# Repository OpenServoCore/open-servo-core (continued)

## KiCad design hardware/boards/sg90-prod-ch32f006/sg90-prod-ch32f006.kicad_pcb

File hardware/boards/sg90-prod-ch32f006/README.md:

# SG90 Servo Controller Board - CH32V006

A compact, high-precision servo controller designed to replace the control circuitry in SG90/MG90 servo clones. This single-sided board fits within a 10x12.5mm footprint while providing advanced features like back-EMF sensing, overcurrent protection, and 0.1-0.2° position precision.

## Features

- **MCU**: CH32V006F8U6 RISC-V microcontroller (48MHz, 32KB flash, 4KB RAM)
- **Motor Driver**: Integrated DRV8837C H-bridge (1.8A peak)
- **Position Sensing**: 12-bit ADC with RC filtering for 0.1-0.2° precision
- **Current Sensing**: 0.1Ω shunt with internal op-amp
- **Protection**: P-channel MOSFET reverse polarity protection (17mΩ RDS(on))
- **Communication**: 2Mbps half-duplex UART over single DATA line
- **Power**: 5V operation, no LDO required
- **Size**: 10x12.5mm, single-sided assembly
- **Debug**: 4-pin SWD interface for programming with WCH-LinkE

## Specifications

- Input Voltage: 4.5-5.5V
- Continuous Current: 200mA (typical servo operation)
- Peak Current: 1A (stall condition)
- Position Resolution: 0.044°/count (4096 counts over 180°)
- PWM Frequency: 10kHz center-aligned
- Communication: 2Mbps half-duplex UART
- Temperature Range: -40°C to +85°C

## Bill of Materials (BOM)

| Ref | Description | Package | LCSC # | Qty | Unit Price @5 | Unit Price @150 | Unit Price @500 |
|-----|-------------|---------|--------|-----|---------------|-----------------|-----------------|
| U1 | CH32V006F8U6 MCU | QFN-20 3x3mm | C42431288 | 1 | $0.2643 | $0.1838 | $0.1537 |
| U2 | DRV8837CDSGR Motor Driver | WSON-8 | C191000 | 1 | $0.098 | $0.0666 | $0.0587 |
| U3 | 74LVC1G07DSFR Buffer | TDFN-6 1x1mm | C42445855 | 1 | $0.0466 | $0.0317 | $0.0280 |
| Q1 | BRCS150P02ZJ P-MOSFET | DFN-6 2x2mm | C22448985 | 1 | $0.0747 | $0.0522 | $0.0466 |
| R1 | 10kΩ 1% | 0603 | Generic | 1 | $0.01 | $0.002 | $0.002 |
| R2 | 0.1Ω 1% 1/4W | 0603/0805 | Generic | 1 | $0.02 | $0.003 | $0.003 |
| R3 | 10kΩ 1% | 0603 | Generic | 1 | $0.01 | $0.002 | $0.002 |
| R4,R5 | 10kΩ 1% | 0603 | Generic | 2 | $0.01 | $0.002 | $0.002 |
| R6,R7 | 0Ω | 0603 | Generic | 2 | $0.01 | $0.001 | $0.001 |
| R8 | 0Ω | 0603 | Generic | 1 | $0.01 | $0.001 | $0.001 |
| R9 | 10kΩ 1% | 0603 | Generic | 1 | $0.01 | $0.002 | $0.002 |
| R10 | 1kΩ 1% | 0603 | Generic | 1 | $0.01 | $0.002 | $0.002 |
| C1,C2 | 100nF 16V X7R | 0603 | Generic | 2 | $0.01 | $0.002 | $0.002 |
| C3 | 1µF 16V X7R | 0603 | Generic | 1 | $0.01 | $0.003 | $0.003 |
| C4,C5 | 10µF 10V X5R | 0603/0805 | Generic | 2 | $0.02 | $0.005 | $0.004 |
| C6 | 100nF 16V X7R | 0603 | Generic | 1 | $0.01 | $0.002 | $0.002 |
| **Components Total** | | | | | **$0.664** | **~$0.35** | **$0.326** |
| **PCB** | 10x12.5mm 4-layer | - | - | 1 | **$1.40** | **$0.25** | **$0.11** |
| **TOTAL per board** | | | | | **$2.064** | **$0.60** | **$0.436** |
| **TOTAL** | | | | | **$10.32** | **$90.00** | **$218.00** |

### Cost Breakdown by Quantity

#### Prototype Run (5 boards)
- Components (5 sets): $0.664 × 5 = $3.32
- PCB (5 boards): $2.00 + $5.00 shipping = $7.00
- **Total for 5 boards: $10.32**
- **Cost per board: $2.06**
- **Selling at $3/board: $15 revenue - Profit: $4.68 (45% margin)**
- **Selling at $5/board: $25 revenue - Profit: $14.68 (142% margin)**

#### Small Production (150 boards)
- Components (150 sets): ~$0.35 × 150 = $52.50
- PCB (150 boards): $32.00 + $5.00 shipping = $37.00
- **Total for 150 boards: $89.50**
- **Cost per board: $0.60**
- **Selling at $2-3/board: $300-450 revenue**
- **Gross profit: $210.50-360.50**

#### Medium Production (500 boards)
- Components (500 sets): $0.326 × 500 = $163.00
- PCB (500 boards): $50.20 + $5.00 shipping = $55.20
- **Total for 500 boards: $218.20**
- **Cost per board: $0.44**
- **Selling at $2/board: $1,000 revenue**
- **Gross profit: $781.80 (358% markup!)**

*Prices shown are from LCSC in USD. Passive component prices are estimates for generic parts.*

## Pinout

### Power Connector (J1) - 3 pins
1. V_IN (5V)
2. DATA (Half-duplex UART, 2Mbps)
3. GND

### Motor Connector (J3) - 2 wire pads
1. MOT_A - Motor terminal A (7.4mm spacing)
2. MOT_B - Motor terminal B

### Potentiometer Connector (J2) - 3 pads
1. POT_VCC - Potentiometer power (5V)
2. POT_WIPER - Position feedback
3. POT_GND - Potentiometer ground

### Debug Interface (J4) - 4 pads, 1.27mm pitch
1. 5V - Power from debugger
2. GND - Ground
3. SWDIO - Single-wire debug
4. NC - Not connected

## Design Notes

### Power Architecture
- Single 5V rail operation eliminates need for LDO
- P-channel MOSFET provides reverse polarity protection with only 17mV drop at 1A
- Bulk capacitance (2x10µF) handles motor transients
- No ferrite bead needed due to synchronized ADC sampling

### ADC Precision
- 12-bit ADC provides 22.8 counts per degree (0.044°/count theoretical)
- RC filter (1kΩ + 100nF) on POT input reduces wiper noise
- 4-16x oversampling in firmware improves effective resolution
- Center-aligned PWM with mid-duty ADC sampling avoids switching noise

### Current Sensing
- 0.1Ω shunt resistor in series with motor ground
- Internal op-amp amplifies voltage drop
- ADC watchdog enables hardware overcurrent protection
- Kelvin connections (0Ω resistors R6,R7) for accurate sensing

### Communication
- Half-duplex UART at 2Mbps over single DATA line
- 74LVC1G07 open-drain buffer enables bidirectional communication
- 10kΩ pullup (R1) sized for 2Mbps operation
- Compatible with standard servo protocols

## Assembly

This board is designed for single-sided assembly, making it ideal for:
- Hot plate reflow
- Hot air station
- IR oven
- JLCPCB assembly service

All components are on the top side with no vias in pads.

## Programming

Program using WCH-LinkE debugger/programmer:
- Supports 5V target voltage
- Single-wire debug (SWD) interface
- Compatible with MounRiver Studio IDE
- printf debugging available over SWD

## Mechanical Integration

The board is designed to fit inside standard SG90 servo cases:
- Motor wires solder directly to MOT_A/MOT_B pads
- Potentiometer wires connect to J2
- Servo cable connects to J1
- Debug pads accessible through case opening

## Performance Targets

- Position accuracy: ±0.1-0.2°
- Position resolution: 0.044°
- Update rate: 10kHz
- Current limit: 1A (configurable via firmware)
- Continuous operation: 200mA
- Response time: <1ms
- Backdrive detection: Yes (via back-EMF)

## Manufacturing

Optimized for low-cost production:
- Total BOM cost: ~$0.43 at 500 qty
- Single-sided assembly reduces assembly cost
- Standard 0603 passives (except current shunt)
- All components available from LCSC
- 4-layer PCB for better thermal management

## TODO / Future Improvements

### Critical Values to Double-Check Before PCB Routing
- [ ] **Current shunt (R2):** Verify 0.1Ω gives good ADC range (0-330mV at 1A through 3.3x op-amp gain)
- [ ] **Voltage dividers (R4/R5):** Confirm 10kΩ divider properly scales 5V motor to ADC range
- [ ] **UART pullup (R1):** Verify 10kΩ optimal for 2Mbps half-duplex
- [ ] **RC filter (R10/C6):** Check 1kΩ + 100nF = 1.6kHz cutoff for POT noise
- [ ] **Bulk caps (C4/C5):** Confirm 2x10µF sufficient for motor transients
- [ ] **P-MOSFET RDS(on):** Verify 17mΩ = 17mV drop at 1A peak is acceptable
- [ ] **Motor pad spacing:** Confirm 7.4mm (3.7mm each side from center)
- [ ] **Debug pad pitch:** Verify 1.27mm for pogo pins
- [ ] **Package sizes:** Verify all footprints match actual parts (especially QFN-20)

### Rev B Changes
1. **Add test points on back side**
   - Add second 1x4 array at 1.27mm pitch (same as debug interface)
   - Uses same pogo pin clip for both programming and testing
   - **Debug array (1x4):** 5V, GND, SWDIO, NC (existing)
   - **Test array (1x4):** SEN_I, SEN_POT, PWM_A, V_MCU
   - Both arrays accessible from back when installed in servo
   - *Rationale: Single pogo clip tool works for both debug and test*

2. **Add ESD protection**
   - TVS diode on DATA line (SOD-523 or 0402 package)
   - Protects against ESD during cable plug/unplug
   - Suggested part: PESD5V0S1BL or similar 5.5V TVS (~$0.05)

3. **Consider fiducial marker**
   - Single 1mm fiducial for JLCPCB assembly alignment
   - Only if assembly house requires it

### Firmware Features (Planned)
- Backlash compensation
- Temperature compensation
- Position calibration LUT
- Multi-drop addressing
- Synchronized motion commands

## License

[Add your license here]

## Author

[Add author information here]

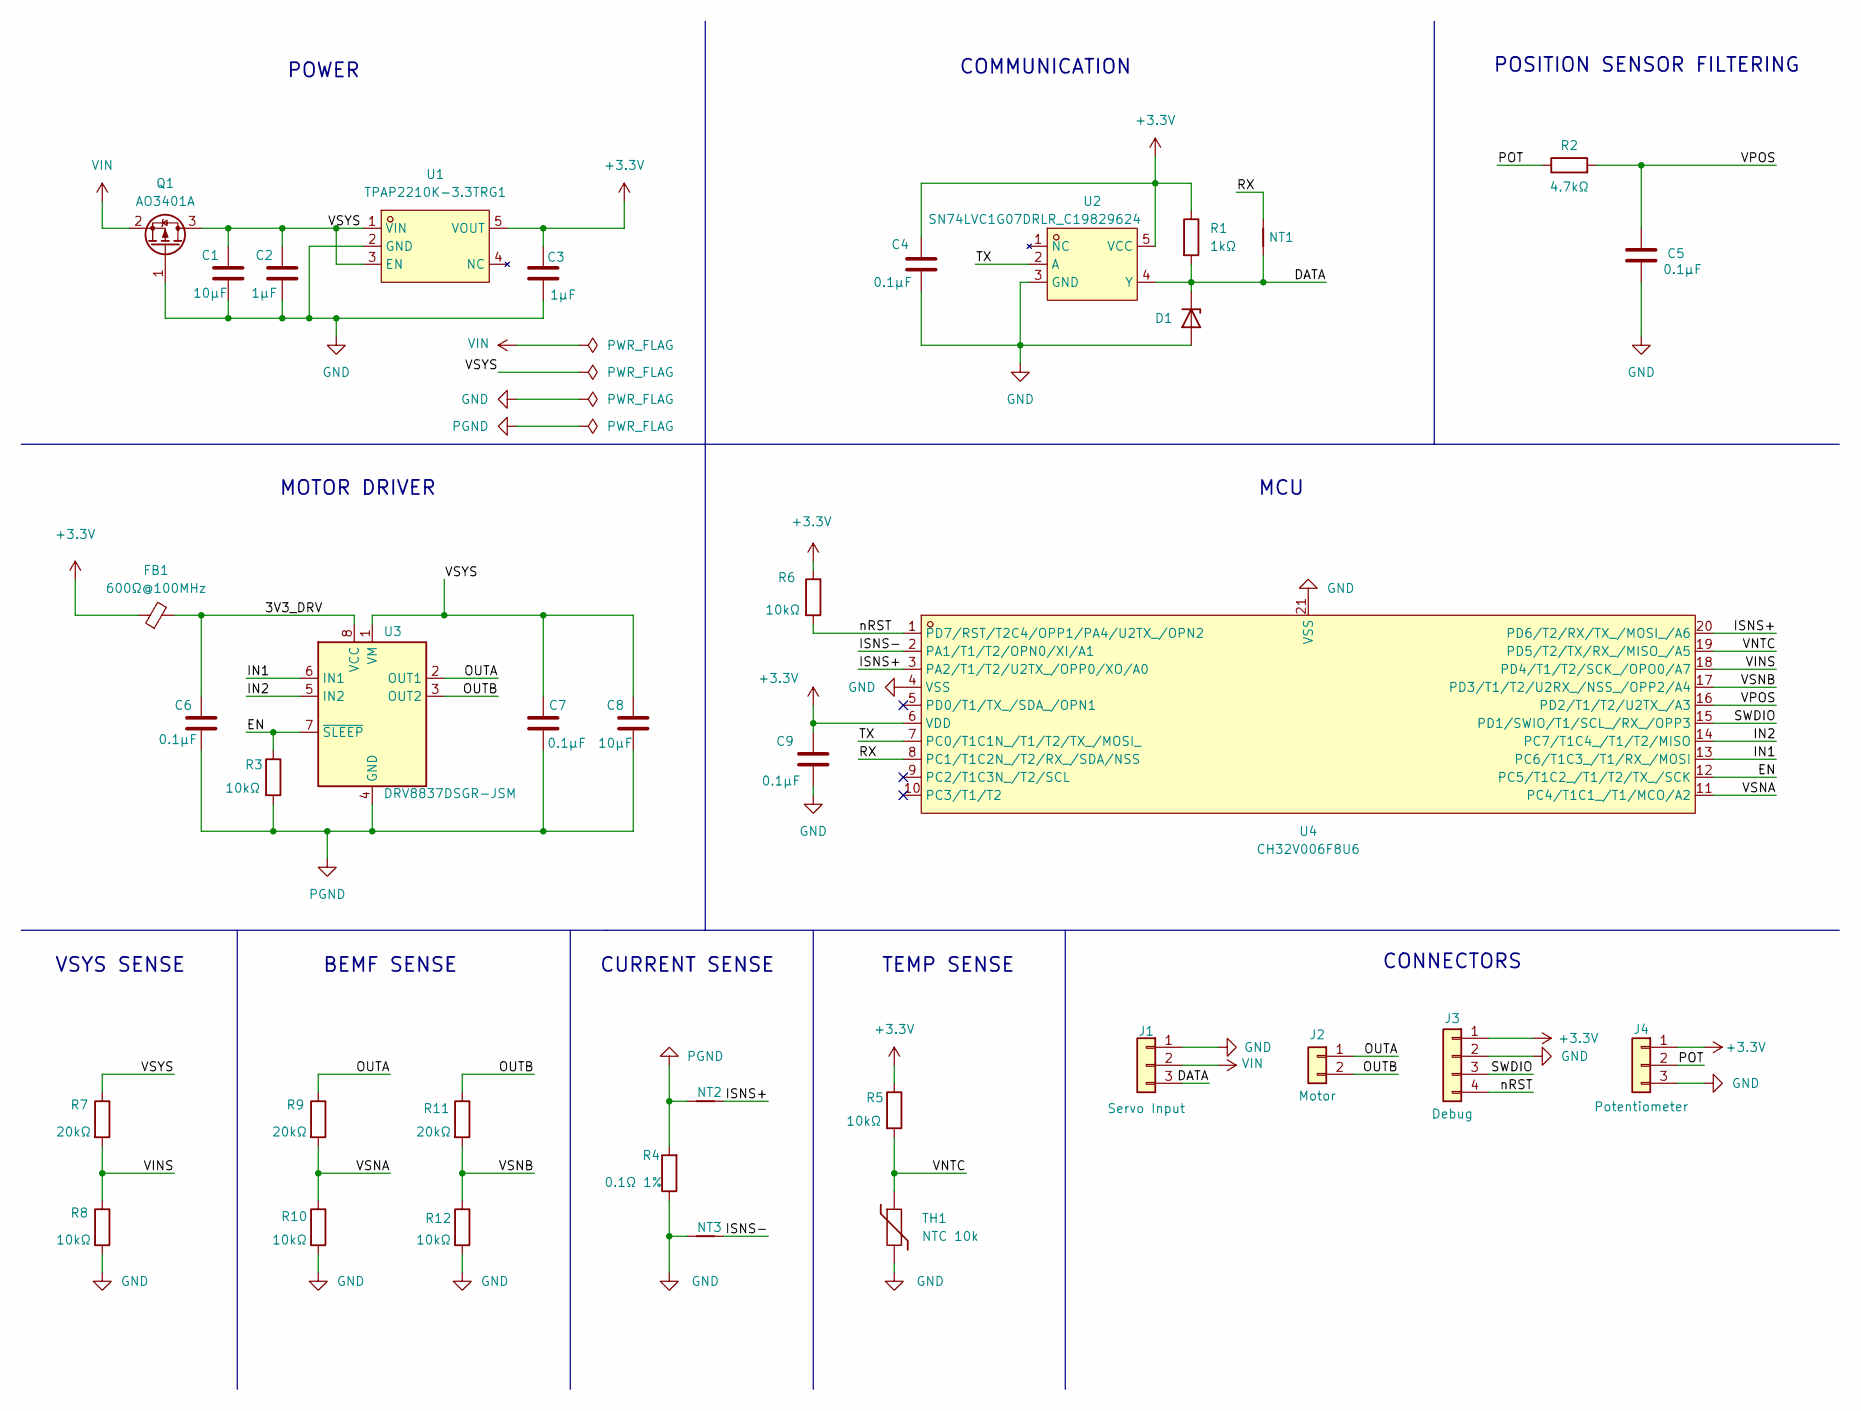
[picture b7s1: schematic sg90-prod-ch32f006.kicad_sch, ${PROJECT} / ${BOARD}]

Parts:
C1, C8: 10µF; C_0603_1608Metric
C2, C3: 1µF; C_0402_1005Metric
C4, C5, C6, C7, C9: 0.1µF; C_0402_1005Metric
D1: PESD5V0L1UL; D_SOD-882
FB1: 600Ω@100MHz; L_0603_1608Metric
J1: Servo Input; Servo_Output_Pads
J2: Motor; Motor_Wire_Pads
J3: Debug; Debug_Pads_1x4_P1.27mm
J4: Potentiometer; Pot_Wire_Pads
NT1, NT2, NT3: NetTie_2; NetTie-2_SMD_0.2mm
Q1: AO3401A; SOT-23
R1: 1kΩ; R_0402_1005Metric
R2: 4.7kΩ; R_0402_1005Metric
R3, R5, R6, R8, R10, R12: 10kΩ; R_0402_1005Metric
R4: 0.1Ω 1%; R_1206_3216Metric
R7, R9, R11: 20kΩ; R_0402_1005Metric
TH1: NTC 10k; R_0402_1005Metric
U1: TPAP2210K-3.3TRG1; SOT-23-5_L2.9-W1.6-P0.95-LS2.8-BR; LCSC Part C49190789
U2: SN74LVC1G07DRLR_C19829624; SOT-553-5_L1.6-W1.2-P0.50-LS1.6-BL; LCSC Part C19829624
U3: DRV8837DSGR-JSM; WSON-8-1EP_2x2mm_P0.5mm_EP0.9x1.6mm; LCSC C22447132
U4: CH32V006F8U6; UQFN-20_L3.0-W3.0-P0.40-BL-EP1.7; LCSC Part C42431288

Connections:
+3.3V: C3.1, C4.1, C9.1, FB1.1, J3.1, J4.1, R1.1, R5.1, R6.1, U1.5 (VOUT), U2.5 (VCC), U4.6 (VDD)
/3V3_DRV: C6.1, FB1.2, U3.8 (VCC)
/DATA: D1.1 (K), J1.3, NT1.2, R1.2, U2.4 (Y)
/EN: R3.1, U3.7 (~SLEEP), U4.12 (PC5/T1C2_/T1/T2/TX_/SCK)
/IN1: U3.6 (IN1), U4.13 (PC6/T1C3_/T1/RX_/MOSI)
/IN2: U3.5 (IN2), U4.14 (PC7/T1C4_/T1/T2/MISO)
/ISNS+: NT2.1, U4.3 (PA2/T1/T2/U2TX_/OPP0/XO/A0), U4.20 (PD6/T2/RX/TX_/MOSI_/A6)
/ISNS-: NT3.1, U4.2 (PA1/T1/T2/OPN0/XI/A1)
/OUTA: J2.1, R9.1, U3.2 (OUT1)
/OUTB: J2.2, R11.1, U3.3 (OUT2)
/POT: J4.2, R2.1
/RX: NT1.1, U4.8 (PC1/T1C2N_/T2/RX_/SDA/NSS)
/SWDIO: J3.3, U4.15 (PD1/SWIO/T1/SCL_/RX_/OPP3)
/TX: U2.2 (A), U4.7 (PC0/T1C1N_/T1/T2/TX_/MOSI_)
/VINS: R7.2, R8.1, U4.18 (PD4/T1/T2/SCK_/OPO0/A7)
/VNTC: R5.2, TH1.1, U4.19 (PD5/T2/TX/RX_/MISO_/A5)
/VPOS: C5.1, R2.2, U4.16 (PD2/T1/T2/U2TX_/A3)
/VSNA: R9.2, R10.1, U4.11 (PC4/T1C1_/T1/MCO/A2)
/VSNB: R11.2, R12.1, U4.17 (PD3/T1/T2/U2RX_/NSS_/OPP2/A4)
/VSYS: C1.1, C2.1, C7.1, C8.1, Q1.3 (D), R7.1, U1.1 (VIN), U1.3 (EN), U3.1 (VM)
/nRST: J3.4, R6.2, U4.1 (PD7/RST/T2C4/OPP1/PA4/U2TX_/OPN2)
GND: C1.2, C2.2, C3.2, C4.2, C5.2, C9.2, D1.2 (A), J1.1, J3.2, J4.3, NT3.2, Q1.1 (G), R4.1, R8.2, R10.2, R12.2, TH1.2, U1.2 (GND), U2.3 (GND), U4.4 (VSS), U4.21 (VSS)
PGND: C6.2, C7.2, C8.2, NT2.2, R3.2, R4.2, U3.4 (GND), U3.9 (GND)
VIN: J1.2, Q1.2 (S)

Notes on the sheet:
VSYS SENSE
POWER
MOTOR DRIVER
BEMF SENSE
CONNECTORS
TEMP SENSE
CURRENT SENSE
COMMUNICATION
MCU
POSITION SENSOR FILTERING

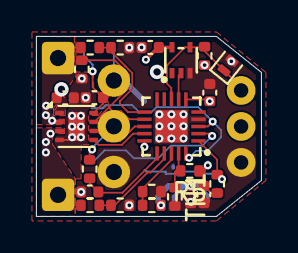
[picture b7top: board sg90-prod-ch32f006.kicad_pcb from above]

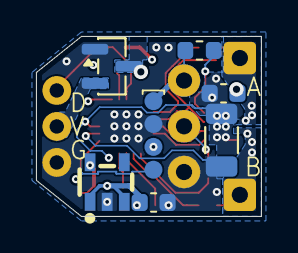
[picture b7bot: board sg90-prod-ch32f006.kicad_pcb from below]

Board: 6 copper layers, 12.5 x 10.0 mm, 36 parts (11 on the bottom side), 24 nets.

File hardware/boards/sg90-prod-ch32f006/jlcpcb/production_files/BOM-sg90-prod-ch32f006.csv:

Comment,Designator,Footprint,LCSC,Quantity
0.1µF,"C4,C5,C6,C7,C9",C_0402_1005Metric,C1525,5
0.1Ω 1%,R4,R_1206_3216Metric,C25334,1
10kΩ,"R10,R12,R3,R5,R6,R8",R_0402_1005Metric,C25744,6
10µF,"C1,C8",C_0603_1608Metric,C96446,2
1kΩ,R1,R_0402_1005Metric,C11702,1
1µF,"C2,C3",C_0402_1005Metric,C52923,2
20kΩ,"R11,R7,R9",R_0402_1005Metric,C25764,3
4.7kΩ,R2,R_0402_1005Metric,C25900,1
600Ω@100MHz,FB1,L_0603_1608Metric,C1002,1
AO3401A,Q1,SOT-23,C15127,1
CH32V006F8U6,U4,UQFN-20_L3.0-W3.0-P0.40-BL-EP1.7,C42431288,1
DRV8837DSGR-JSM,U3,WSON-8-1EP_2x2mm_P0.5mm_EP0.9x1.6mm,C22447132,1
NTC 10k,TH1,R_0402_1005Metric,C77131,1
PESD5V0L1UL,D1,D_SOD-882,C3001948,1
SN74LVC1G07DRLR_C19829624,U2,SOT-553-5_L1.6-W1.2-P0.50-LS1.6-BL,C19829624,1
TPAP2210K-3.3TRG1,U1,SOT-23-5_L2.9-W1.6-P0.95-LS2.8-BR,C49190789,1

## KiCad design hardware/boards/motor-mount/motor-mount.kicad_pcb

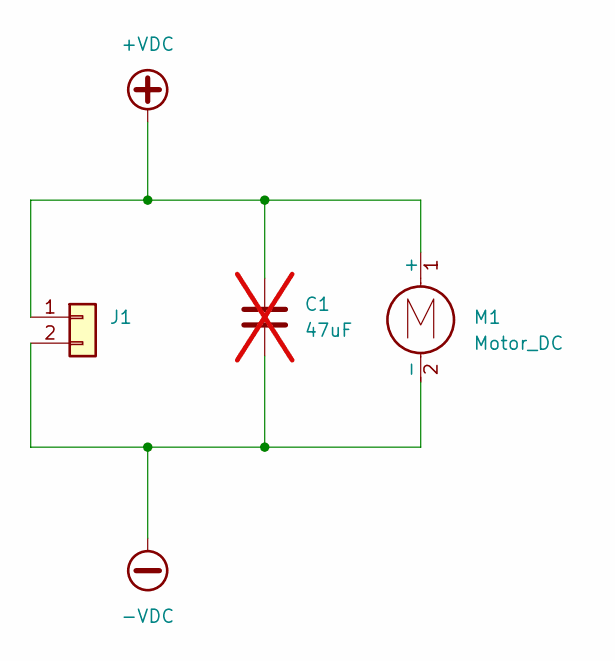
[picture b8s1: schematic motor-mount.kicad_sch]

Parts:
C1: 47uF; C_1206_3216Metric; not fitted
J1: PinHeader_1x02_P2.54mm_Vertical
M1: Motor_DC; SG90_Motor

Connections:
+VDC: C1.1, J1.1, M1.1 (+)
-VDC: C1.2, J1.2, M1.2 (-)

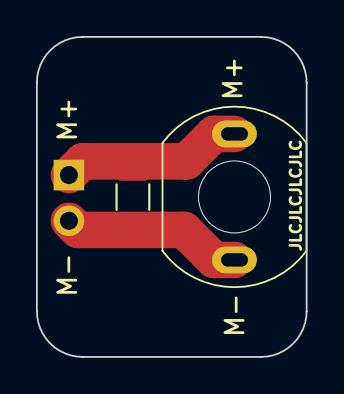
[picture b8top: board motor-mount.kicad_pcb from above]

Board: 2 copper layers, 15.0 x 17.8 mm, 3 parts (1 on the bottom side), 2 nets.

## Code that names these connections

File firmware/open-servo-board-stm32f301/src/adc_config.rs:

//! Feature-gated ADC channel configuration.
//!
//! The ADC sequence length depends on enabled features:
//! - Always: VREFINT, position (ch1)
//! - current-sense-bus: current sense (ch2)
//! - voltage-sense-motor: voltage dividers (ch3, ch4)
//! - temp-sense-mcu: internal temp sensor (ch16)
//! - temp-sense-motor: NTC thermistor (ch5)

use open_servo_macros::AdcChannels;

#[derive(AdcChannels)]
#[adc_channels(buffer = "AdcBuffer", count = "ADC_CHANNEL_COUNT")]
pub struct Channels<'a> {
    buf: &'a [u16],

    /// VREFINT (internal voltage reference).
    #[channel(name = "VREFINT")]
    _vrefint: (),

    /// Position sensor (PA0, ADC1_IN1).
    #[channel(name = "POSITION")]
    _position: (),

    /// Current sense (PA1, ADC1_IN2).
    #[cfg(feature = "current-sense-bus")]
    #[channel(name = "CURRENT")]
    _current: (),

    /// Motor voltage A (PA2, ADC1_IN3).
    #[cfg(feature = "voltage-sense-motor")]
    #[channel(name = "VOLTAGE_A")]
    _voltage_a: (),

    /// Motor voltage B (PA3, ADC1_IN4).
    #[cfg(feature = "voltage-sense-motor")]
    #[channel(name = "VOLTAGE_B")]
    _voltage_b: (),

    /// Motor temperature NTC (PA4, ADC1_IN5).
    #[cfg(feature = "temp-sense-motor")]
    #[channel(name = "MOTOR_TEMP")]
    _motor_temp: (),

    /// MCU internal temperature sensor (ADC1_IN16).
    #[cfg(feature = "temp-sense-mcu")]
    #[channel(name = "MCU_TEMP")]
    _mcu_temp: (),
}
